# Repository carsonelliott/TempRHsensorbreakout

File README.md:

# TempRHsensorbreakout
SHTC3 breakout board schematics and gerbers

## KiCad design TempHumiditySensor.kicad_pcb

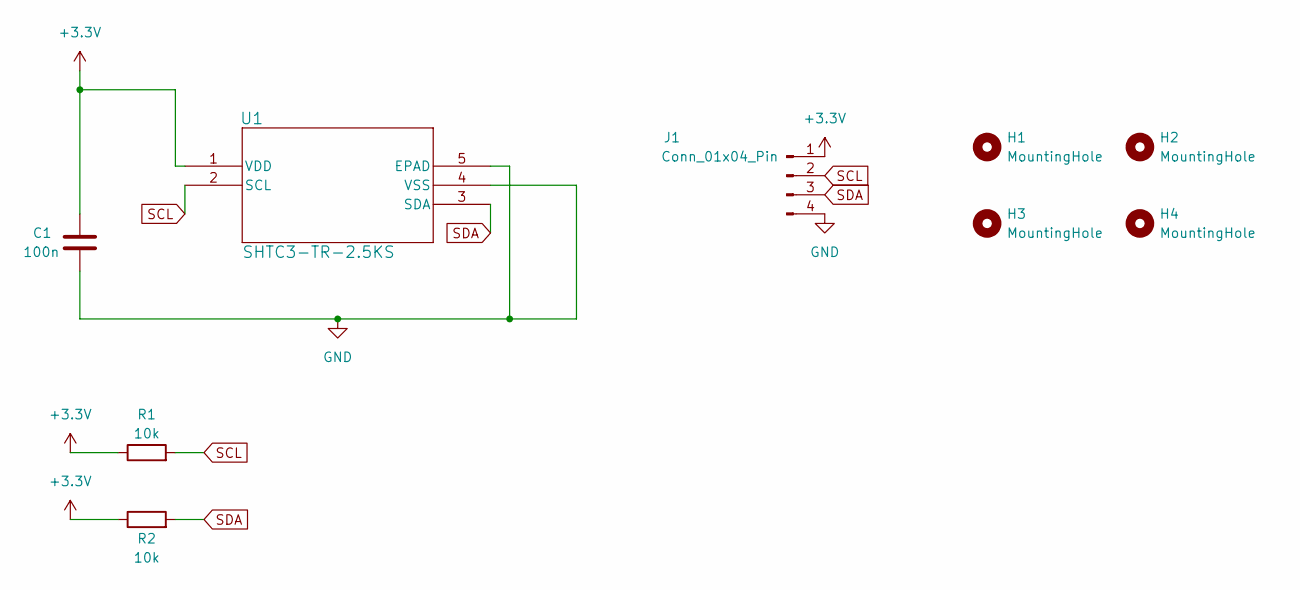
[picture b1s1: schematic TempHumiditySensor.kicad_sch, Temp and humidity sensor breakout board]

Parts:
C1: 100n; C_0402_1005Metric
H1, H2, H3, H4: MountingHole; MountingHole_2.1mm
J1: Conn_01x04_Pin; PinHeader_1x04_P1.27mm_Vertical
R1, R2: 10k; R_0402_1005Metric
U1: SHTC3-TR-2.5KS; SHTC3_SEN

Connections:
+3.3V: C1.1, J1.1, R1.1, R2.1, U1.1 (VDD)
GND: C1.2, J1.4, U1.4 (VSS), U1.5 (EPAD)
SCL: J1.2, R1.2, U1.2 (SCL)
SDA: J1.3, R2.2, U1.3 (SDA)

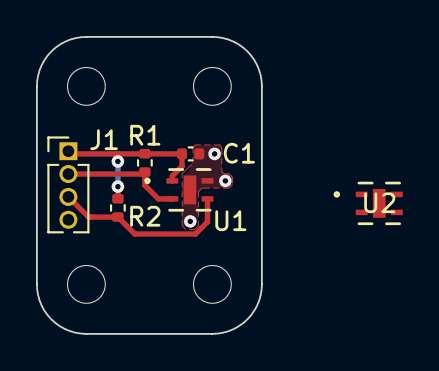
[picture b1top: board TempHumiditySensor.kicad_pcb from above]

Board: 2 copper layers, 12.5 x 16.5 mm, 10 parts (0 on the bottom side), 4 nets.

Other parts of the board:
U2: SHTC3-TR-2.5KS; SHTC3_SEN
